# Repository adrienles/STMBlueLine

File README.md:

# STMBlueLine
STM32H750 M.2 module for audio applications

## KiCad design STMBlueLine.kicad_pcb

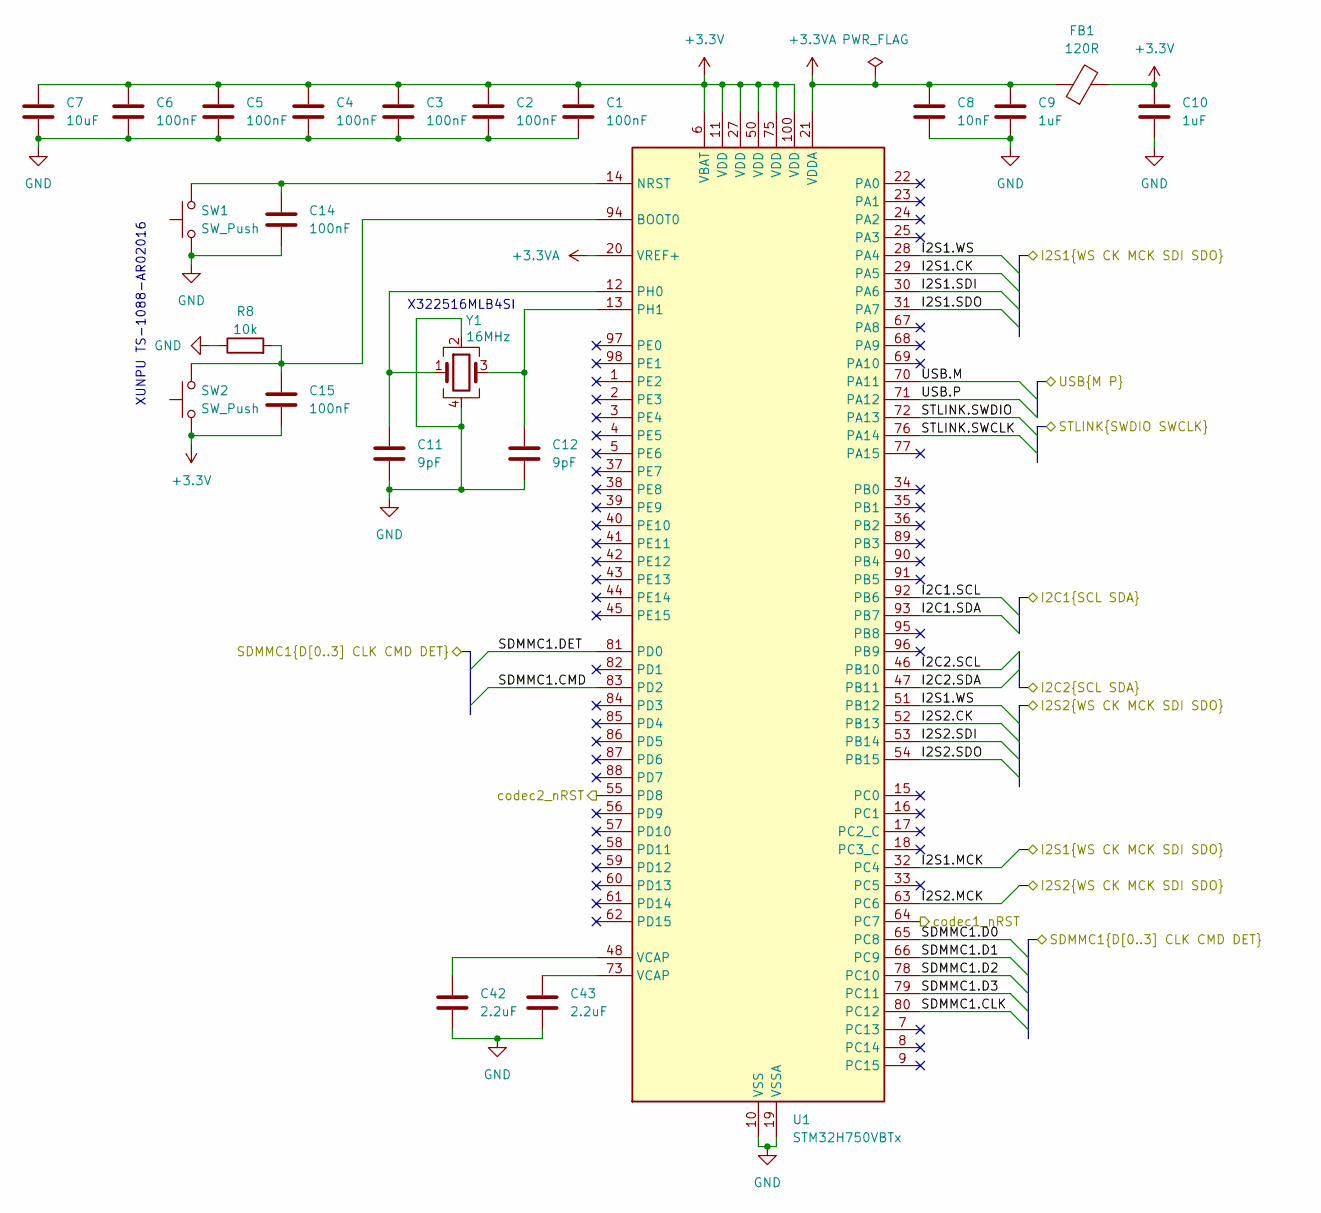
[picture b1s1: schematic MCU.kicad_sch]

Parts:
C1, C2, C3, C4, C5, C6, C14, C15: 100nF; C_0402_1005Metric
C7: 10uF; C_0402_1005Metric
C8: 10nF; C_0402_1005Metric
C9, C10: 1uF; C_0402_1005Metric
C11, C12: 9pF; C_0402_1005Metric
C42, C43: 2.2uF; C_0402_1005Metric
FB1: 120R; R_0402_1005Metric
R8: 10k; R_0402_1005Metric
SW1, SW2: SW_Push; SW_TS-1088-AR02016
U1: STM32H750VBTx; LQFP-100_14x14mm_P0.5mm
Y1: 16MHz; Crystal_SMD_3225-4Pin_3.2x2.5mm

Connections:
+3.3V: C1.1, C2.1, C3.1, C4.1, C5.1, C6.1, C7.1, C10.1, C15.2, FB1.2, SW2.1, U1.6 (VBAT), U1.11 (VDD), U1.27 (VDD), U1.50 (VDD), U1.75 (VDD), U1.100 (VDD); also elsewhere on the board
+3.3VA: C8.1, C9.1, FB1.1, U1.20 (VREF+), U1.21 (VDDA); also elsewhere on the board
/Codec (In-Out Channels 1 & 2)/I2C.SCL: U1.92 (PB6); also elsewhere on the board
/Codec (In-Out Channels 1 & 2)/I2C.SDA: U1.93 (PB7); also elsewhere on the board
/Codec (In-Out Channels 1 & 2)/I2S.CK: U1.29 (PA5); also elsewhere on the board
/Codec (In-Out Channels 1 & 2)/I2S.MCK: U1.32 (PC4); also elsewhere on the board
/Codec (In-Out Channels 1 & 2)/I2S.SDI: U1.30 (PA6); also elsewhere on the board
/Codec (In-Out Channels 1 & 2)/I2S.SDO: U1.31 (PA7); also elsewhere on the board
/Codec (In-Out Channels 1 & 2)/I2S.WS: U1.28 (PA4), U1.51 (PB12); also elsewhere on the board
/Codec (In-Out Channels 1 & 2)/nRST: U1.64 (PC7); also elsewhere on the board
/Codec (In-Out Channels 3 & 4)/I2C.SCL: U1.46 (PB10); also elsewhere on the board
/Codec (In-Out Channels 3 & 4)/I2C.SDA: U1.47 (PB11); also elsewhere on the board
/Codec (In-Out Channels 3 & 4)/I2S.CK: U1.52 (PB13); also elsewhere on the board
/Codec (In-Out Channels 3 & 4)/I2S.MCK: U1.63 (PC6); also elsewhere on the board
/Codec (In-Out Channels 3 & 4)/I2S.SDI: U1.53 (PB14); also elsewhere on the board
/Codec (In-Out Channels 3 & 4)/I2S.SDO: U1.54 (PB15); also elsewhere on the board
/Codec (In-Out Channels 3 & 4)/nRST: U1.55 (PD8); also elsewhere on the board
/MCU/SDMMC1.CLK: U1.80 (PC12); also elsewhere on the board
/MCU/SDMMC1.CMD: U1.83 (PD2); also elsewhere on the board
/MCU/SDMMC1.D0: U1.65 (PC8); also elsewhere on the board
/MCU/SDMMC1.D1: U1.66 (PC9); also elsewhere on the board
/MCU/SDMMC1.D2: U1.78 (PC10); also elsewhere on the board
/MCU/SDMMC1.D3: U1.79 (PC11); also elsewhere on the board
/MCU/SDMMC1.DET: U1.81 (PD0); also elsewhere on the board
/MCU/STLINK.SWCLK: U1.76 (PA14); also elsewhere on the board
/MCU/STLINK.SWDIO: U1.72 (PA13); also elsewhere on the board
/MCU/USB.M: U1.70 (PA11); also elsewhere on the board
/MCU/USB.P: U1.71 (PA12); also elsewhere on the board
GND: C1.2, C2.2, C3.2, C4.2, C5.2, C6.2, C7.2, C8.2, C9.2, C10.2, C11.2, C12.2, C14.2, C42.2, C43.2, R8.1, SW1.1, U1.10 (VSS), U1.19 (VSSA), U1.26 (VSS), U1.49 (VSS), U1.74 (VSS), U1.99 (VSS), Y1.2, Y1.4; also elsewhere on the board
unnamed: C42.1, U1.48 (VCAP)
unnamed: C43.1, U1.73 (VCAP)
unnamed: C15.1, R8.2, SW2.2, U1.94 (BOOT0)
unnamed: C14.1, SW1.2, U1.14 (NRST)
unnamed: C11.1, U1.12 (PH0), Y1.1
unnamed: C12.1, U1.13 (PH1), Y1.3

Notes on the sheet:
XUNPU TS-1088-AR02016
X322516MLB4SI

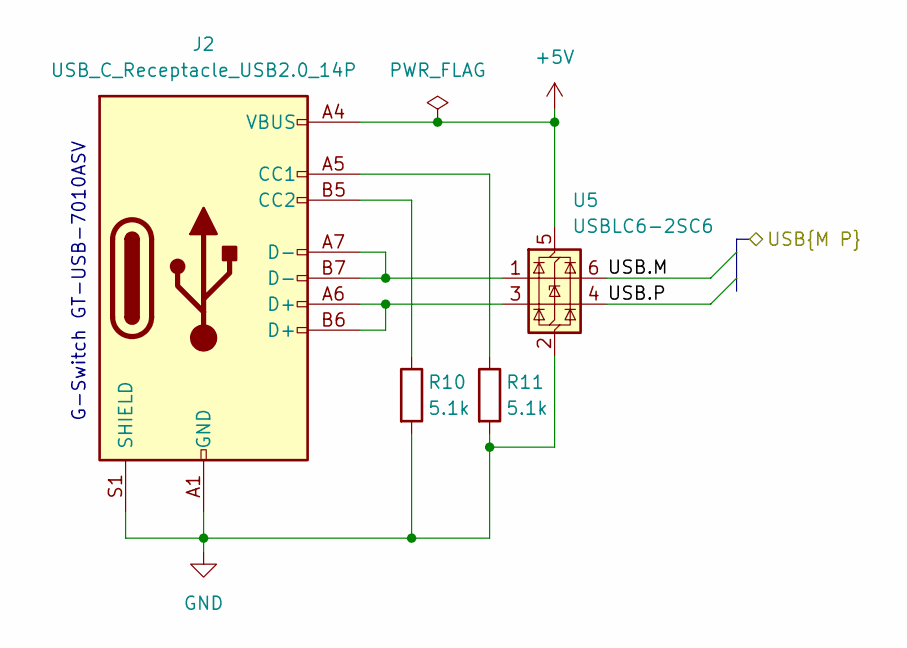
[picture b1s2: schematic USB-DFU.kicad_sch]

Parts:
J2: USB_C_Receptacle_USB2.0_14P; USB_C_Receptacle_G-Switch_GT-USB-7010ASV
R10, R11: 5.1k; R_0402_1005Metric
U5: USBLC6-2SC6; SOT-23-6

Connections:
+5V: J2.A4 (VBUS), J2.A9 (VBUS), J2.B4 (VBUS), J2.B9 (VBUS), U5.5 (VBUS); also elsewhere on the board
/MCU/USB.M: U5.6 (I/O1); also elsewhere on the board
/MCU/USB.P: U5.4 (I/O2); also elsewhere on the board
GND: J2.A1 (GND), J2.A12 (GND), J2.B1 (GND), J2.B12 (GND), J2.S1 (SHIELD), R10.2, R11.2, U5.2 (GND); also elsewhere on the board
unnamed: J2.A5 (CC1), R11.1
unnamed: J2.B5 (CC2), R10.1
unnamed: J2.A6 (D+), J2.B6 (D+), U5.3 (I/O2)
unnamed: J2.A7 (D-), J2.B7 (D-), U5.1 (I/O1)

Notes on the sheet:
G-Switch GT-USB-7010ASV

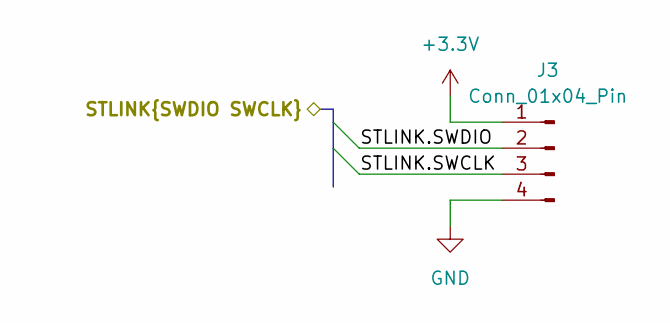
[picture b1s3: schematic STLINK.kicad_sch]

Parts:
J3: Conn_01x04_Pin; PinHeader_1x04_P2.54mm_Vertical

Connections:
+3.3V: J3.1; also elsewhere on the board
/MCU/STLINK.SWCLK: J3.3; also elsewhere on the board
/MCU/STLINK.SWDIO: J3.2; also elsewhere on the board
GND: J3.4; also elsewhere on the board

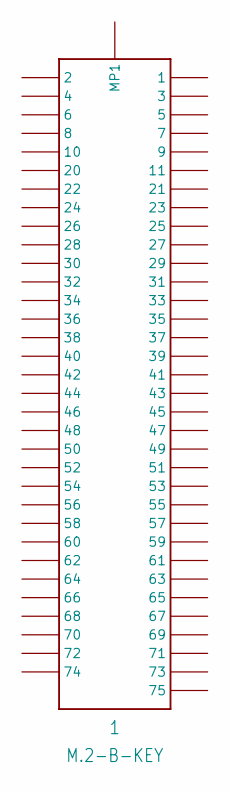
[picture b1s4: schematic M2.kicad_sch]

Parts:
1: M.2-B-KEY

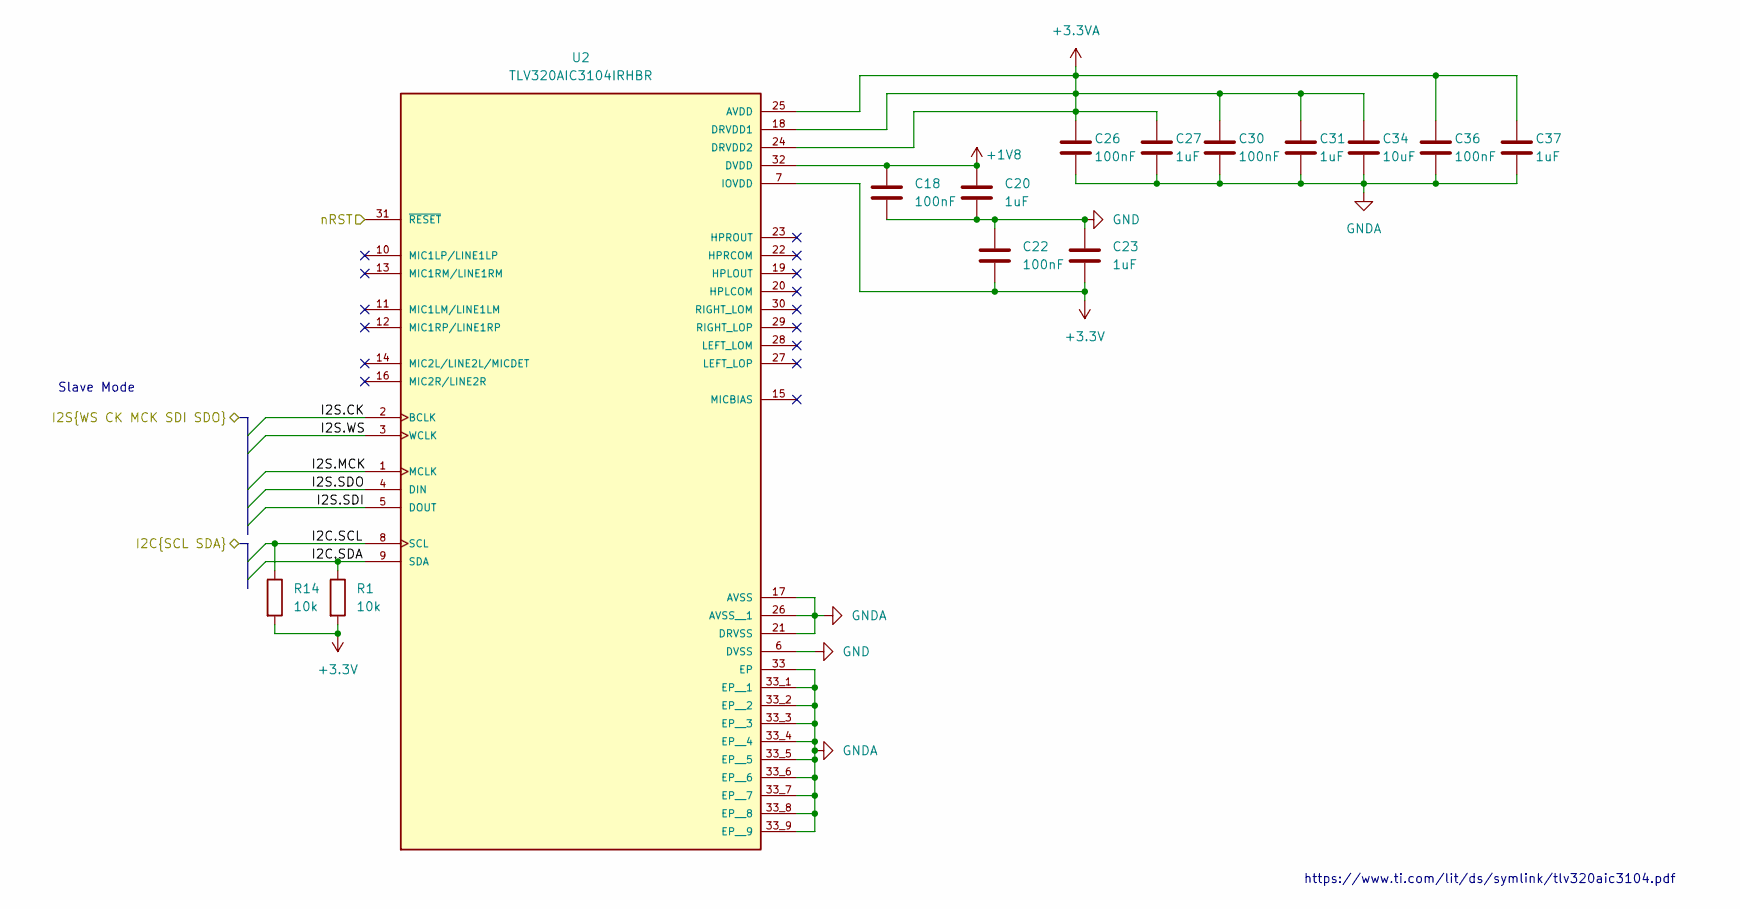
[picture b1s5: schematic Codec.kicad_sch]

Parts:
C18, C22, C26, C30, C36: 100nF; C_0402_1005Metric
C20, C23, C27, C31, C37: 1uF; C_0402_1005Metric
C34: 10uF; C_0402_1005Metric
R1, R14: 10k; R_0402_1005Metric
U2: TLV320AIC3104IRHBR; QFN50P500X500X100-33N

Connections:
+1V8: C18.2, C20.2, U2.32 (DVDD); also elsewhere on the board
+3.3V: C22.1, C23.1, R1.2, R14.2, U2.7 (IOVDD); also elsewhere on the board
+3.3VA: C26.2, C27.2, C30.2, C31.2, C34.2, C36.2, C37.2, U2.18 (DRVDD1), U2.24 (DRVDD2), U2.25 (AVDD); also elsewhere on the board
/Codec (In-Out Channels 1 & 2)/I2C.SCL: R14.1, U2.8 (SCL); also elsewhere on the board
/Codec (In-Out Channels 1 & 2)/I2C.SDA: R1.1, U2.9 (SDA); also elsewhere on the board
/Codec (In-Out Channels 1 & 2)/I2S.CK: U2.2 (BCLK); also elsewhere on the board
/Codec (In-Out Channels 1 & 2)/I2S.MCK: U2.1 (MCLK); also elsewhere on the board
/Codec (In-Out Channels 1 & 2)/I2S.SDI: U2.5 (DOUT); also elsewhere on the board
/Codec (In-Out Channels 1 & 2)/I2S.SDO: U2.4 (DIN); also elsewhere on the board
/Codec (In-Out Channels 1 & 2)/I2S.WS: U2.3 (WCLK); also elsewhere on the board
/Codec (In-Out Channels 1 & 2)/nRST: U2.31 (~RESET); also elsewhere on the board
GND: C18.1, C20.1, C22.2, C23.2, U2.6 (DVSS); also elsewhere on the board
GNDA: C26.1, C27.1, C30.1, C31.1, C34.1, C36.1, C37.1, U2.17 (AVSS), U2.21 (DRVSS), U2.26 (AVSS__1), U2.33 (EP), U2.33_1 (EP__1), U2.33_2 (EP__2), U2.33_3 (EP__3), U2.33_4 (EP__4), U2.33_5 (EP__5), U2.33_6 (EP__6), U2.33_7 (EP__7), U2.33_8 (EP__8), U2.33_9 (EP__9); also elsewhere on the board

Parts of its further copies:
C19, C24, C28, C32, C38: 100nF; C_0402_1005Metric
C21, C25, C29, C33, C39: 1uF; C_0402_1005Metric
C35: 10uF; C_0402_1005Metric
R13, R15: 10k; R_0402_1005Metric
U3: TLV320AIC3104IRHBR; QFN50P500X500X100-33N

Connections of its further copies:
+1V8: C19.2, C21.2, U3.32 (DVDD); also elsewhere on the board
+3.3V: C24.1, C25.1, R13.2, R15.2, U3.7 (IOVDD); also elsewhere on the board
+3.3VA: C28.2, C29.2, C32.2, C33.2, C35.2, C38.2, C39.2, U3.18 (DRVDD1), U3.24 (DRVDD2), U3.25 (AVDD); also elsewhere on the board
/Codec (In-Out Channels 3 & 4)/I2C.SCL: R15.1, U3.8 (SCL); also elsewhere on the board
/Codec (In-Out Channels 3 & 4)/I2C.SDA: R13.1, U3.9 (SDA); also elsewhere on the board
/Codec (In-Out Channels 3 & 4)/I2S.CK: U3.2 (BCLK); also elsewhere on the board
/Codec (In-Out Channels 3 & 4)/I2S.MCK: U3.1 (MCLK); also elsewhere on the board
/Codec (In-Out Channels 3 & 4)/I2S.SDI: U3.5 (DOUT); also elsewhere on the board
/Codec (In-Out Channels 3 & 4)/I2S.SDO: U3.4 (DIN); also elsewhere on the board
/Codec (In-Out Channels 3 & 4)/I2S.WS: U3.3 (WCLK)
/Codec (In-Out Channels 3 & 4)/nRST: U3.31 (~RESET); also elsewhere on the board
GND: C19.1, C21.1, C24.2, C25.2, U3.6 (DVSS); also elsewhere on the board
GNDA: C28.1, C29.1, C32.1, C33.1, C35.1, C38.1, C39.1, U3.17 (AVSS), U3.21 (DRVSS), U3.26 (AVSS__1), U3.33 (EP), U3.33_1 (EP__1), U3.33_2 (EP__2), U3.33_3 (EP__3), U3.33_4 (EP__4), U3.33_5 (EP__5), U3.33_6 (EP__6), U3.33_7 (EP__7), U3.33_8 (EP__8), U3.33_9 (EP__9); also elsewhere on the board

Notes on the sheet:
https://www.ti.com/lit/ds/symlink/tlv320aic3104.pdf
Slave Mode

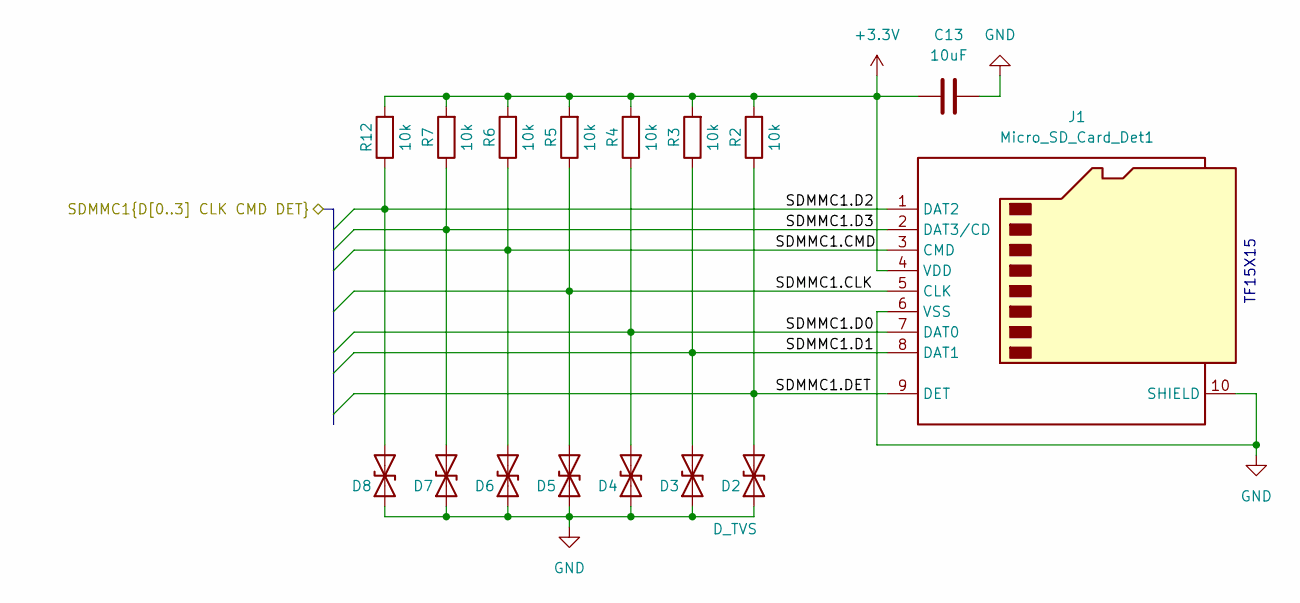
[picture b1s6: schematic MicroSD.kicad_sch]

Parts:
C13: 10uF; C_0402_1005Metric
D2, D3, D4, D5, D6, D7, D8: D_TVS; D_0402_1005Metric
J1: Micro_SD_Card_Det1; TF-SMD_TF-123-ARP9H15
R2, R3, R4, R5, R6, R7, R12: 10k; R_0402_1005Metric

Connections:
+3.3V: C13.1, J1.4 (VDD), R2.2, R3.2, R4.2, R5.2, R6.2, R7.2, R12.2; also elsewhere on the board
/MCU/SDMMC1.CLK: D5.2 (A2), J1.5 (CLK), R5.1; also elsewhere on the board
/MCU/SDMMC1.CMD: D6.2 (A2), J1.3 (CMD), R6.1; also elsewhere on the board
/MCU/SDMMC1.D0: D4.2 (A2), J1.7 (DAT0), R4.1; also elsewhere on the board
/MCU/SDMMC1.D1: D3.2 (A2), J1.8 (DAT1), R3.1; also elsewhere on the board
/MCU/SDMMC1.D2: D8.2 (A2), J1.1 (DAT2), R12.1; also elsewhere on the board
/MCU/SDMMC1.D3: D7.2 (A2), J1.2 (DAT3/CD), R7.1; also elsewhere on the board
/MCU/SDMMC1.DET: D2.2 (A2), J1.9 (DET), R2.1; also elsewhere on the board
GND: C13.2, D2.1 (A1), D3.1 (A1), D4.1 (A1), D5.1 (A1), D6.1 (A1), D7.1 (A1), D8.1 (A1), J1.6 (VSS), J1.10 (SHIELD); also elsewhere on the board

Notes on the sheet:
TF15X15

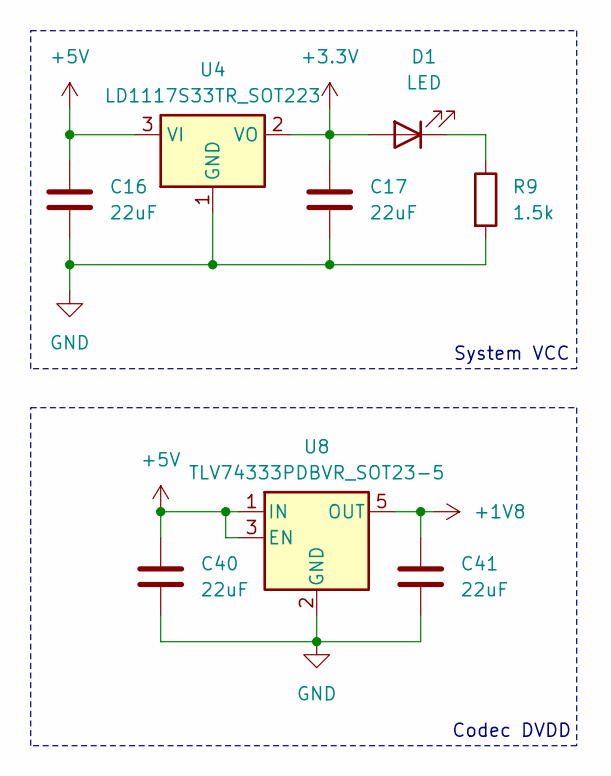
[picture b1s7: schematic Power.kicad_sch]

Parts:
C16, C17, C40, C41: 22uF; C_0402_1005Metric
D1: LED; LED_0402_1005Metric
R9: 1.5k; R_0402_1005Metric
U4: LD1117S33TR_SOT223; SOT-223-3_TabPin2
U8: TLV74333PDBVR_SOT23-5; SOT-23-5

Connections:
+1V8: C41.1, U8.5 (OUT); also elsewhere on the board
+3.3V: C17.1, D1.2 (A), U4.2 (VO); also elsewhere on the board
+5V: C16.1, C40.1, U4.3 (VI), U8.1 (IN), U8.3 (EN); also elsewhere on the board
GND: C16.2, C17.2, C40.2, C41.2, R9.2, U4.1 (GND), U8.2 (GND); also elsewhere on the board
unnamed: D1.1 (K), R9.1

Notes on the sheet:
System VCC
Codec DVDD

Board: 4 copper layers, 80 parts (1 on the bottom side), 43 nets, no tracks yet.

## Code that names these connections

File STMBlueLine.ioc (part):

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Mcu.Name=STM32H750VBTx
Mcu.Package=LQFP100
Mcu.UserName=STM32H750VBTx
PA11.Mode=Device_Only
PA11.Signal=USB_OTG_FS_DM
PA12.Mode=Device_Only
PA12.Signal=USB_OTG_FS_DP
PA13\ (JTMS/SWDIO).Mode=Serial_Wire
PA13\ (JTMS/SWDIO).Signal=DEBUG_JTMS-SWDIO
PA14\ (JTCK/SWCLK).Mode=Serial_Wire
PA14\ (JTCK/SWCLK).Signal=DEBUG_JTCK-SWCLK
PA4.Mode=Full_Duplex_Master
PA4.Signal=I2S1_WS
PA5.Mode=Full_Duplex_Master
PA5.Signal=I2S1_CK
PA6.Mode=Full_Duplex_Master
PA6.Signal=I2S1_SDI
PA7.Mode=Full_Duplex_Master
PA7.Signal=I2S1_SDO
PB10.Mode=I2C
PB10.Signal=I2C2_SCL
PB11.Mode=I2C
PB11.Signal=I2C2_SDA
PB12.Mode=Full_Duplex_Master
PB12.Signal=I2S2_WS
PB13.Mode=Full_Duplex_Master
PB13.Signal=I2S2_CK
PB14.Mode=Full_Duplex_Master
PB14.Signal=I2S2_SDI
PB15.Mode=Full_Duplex_Master
PB15.Signal=I2S2_SDO
PB6.Mode=I2C
PB6.Signal=I2C1_SCL
PB7.Mode=I2C
PB7.Signal=I2C1_SDA
PC10.Mode=SD_4_bits_Wide_bus
PC10.Signal=SDMMC1_D2
PC11.Mode=SD_4_bits_Wide_bus
PC11.Signal=SDMMC1_D3
PC12.Mode=SD_4_bits_Wide_bus
PC12.Signal=SDMMC1_CK
PC4.Mode=Master_Clock_Activated
PC4.Signal=I2S1_MCK
PC5.Signal=GPIO_Output
PC6.Mode=Master_Clock_Activated
PC6.Signal=I2S2_MCK
PC8.Mode=SD_4_bits_Wide_bus
PC8.Signal=SDMMC1_D0
PC9.Mode=SD_4_bits_Wide_bus
PC9.Signal=SDMMC1_D1
PD2.Mode=SD_4_bits_Wide_bus
PD2.Signal=SDMMC1_CMD
PD8.Signal=GPIO_Output
PH0-OSC_IN\ (PH0).Mode=HSE-External-Oscillator
PH0-OSC_IN\ (PH0).Signal=RCC_OSC_IN
PH1-OSC_OUT\ (PH1).Mode=HSE-External-Oscillator
PH1-OSC_OUT\ (PH1).Signal=RCC_OSC_OUT
RCC.SYSCLKFreq_VALUE=64000000
board=custom

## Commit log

2025-02-17 ADD : MIT License Clause
2025-02-17 ADD : KiCad Project
2025-02-19 ADD : Basic MCU, USB, STLINK, uSD schematics
2025-02-21 MOD : KiCad 8.0.1 -> 9.0.0. ADD : Codec power circuitry.
2025-02-21 FIX : uSD Card detect
2025-02-21 ADD : ESD protection for uSD. FIX : uSD pullups
2025-02-21 ADD : Finished codec power and data connections
2025-02-21 ADD : CubeMX pin config
2025-02-22 ADD : Footprint assignment. FIX : Various ERC rules.
2025-02-22 ADD : Rough PCB part placement. MOD : Swapped codec DVDD LDO.
2025-02-22 ADD : PCB Stackup
2025-02-22 ADD : Remaining available 3D models
